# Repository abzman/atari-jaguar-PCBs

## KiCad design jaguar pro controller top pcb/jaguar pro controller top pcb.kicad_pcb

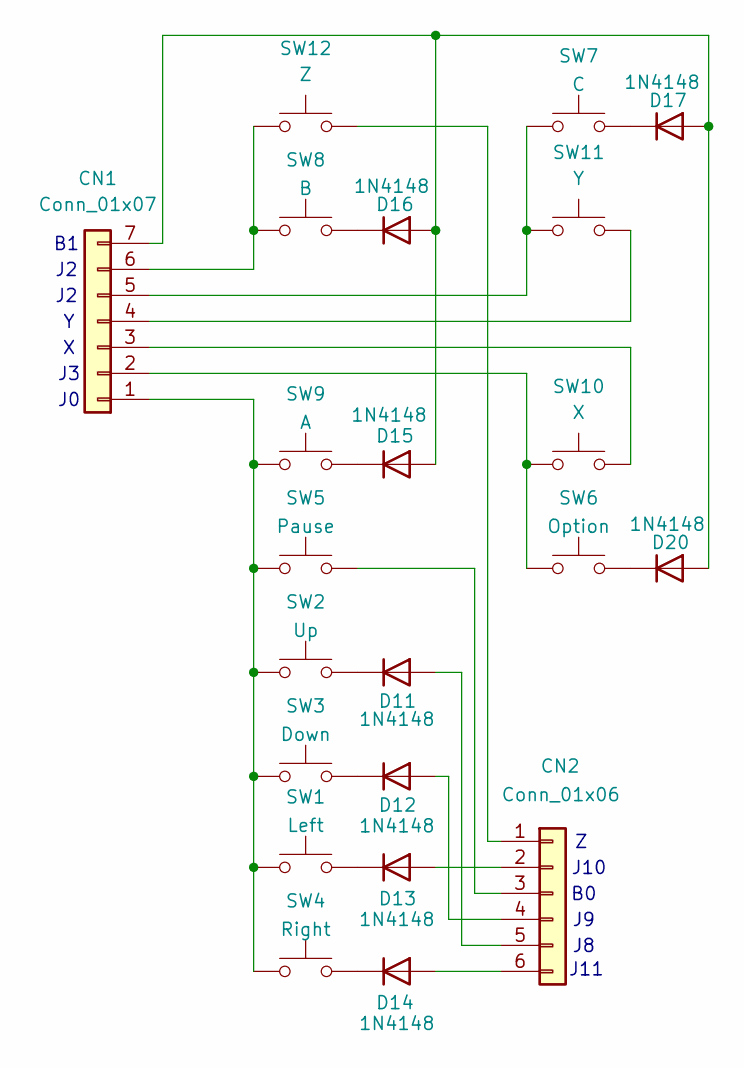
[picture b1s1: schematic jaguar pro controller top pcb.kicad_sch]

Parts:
CN1: Conn_01x07; PinHeader_1x07_P2.00mm_Vertical
CN2: Conn_01x06; PinHeader_1x06_P2.00mm_Vertical
D11, D12, D13, D14, D16, D17, D20: 1N4148; D_DO-35_SOD27_P5.62mm_Horizontal
D15: 1N4148; D_DO-35_SOD27_P9.50mm_Horizontal
SW1: Left; jaguar pro dpad
SW2: Up; jaguar pro dpad
SW3: Down; jaguar pro dpad
SW4: Right; jaguar pro dpad
SW5: Pause; jaguar pro keypad
SW6: Option; jaguar pro keypad
SW7: C; Jaguar pro ABC button
SW8: B; Jaguar pro ABC button
SW9: A; Jaguar pro ABC button
SW10: X; Jaguar pro ABC button
SW11: Y; Jaguar pro ABC button
SW12: Z; Jaguar pro ABC button

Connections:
unnamed: CN2.5, D11.2 (A)
unnamed: D11.1 (K), SW2.2
unnamed: CN2.4, D12.2 (A)
unnamed: D12.1 (K), SW3.2
unnamed: CN2.2, D13.2 (A)
unnamed: D13.1 (K), SW1.2
unnamed: CN2.6, D14.2 (A)
unnamed: D14.1 (K), SW4.2
unnamed: CN1.7, D15.2 (A), D16.2 (A), D17.2 (A), D20.2 (A)
unnamed: D15.1 (K), SW9.2
unnamed: D16.1 (K), SW8.2
unnamed: D17.1 (K), SW7.2
unnamed: D20.1 (K), SW6.1
unnamed: CN1.1, SW1.1, SW2.1, SW3.1, SW4.1, SW5.2, SW9.1
unnamed: CN1.2, SW6.2, SW10.1
unnamed: CN1.3, SW10.2
unnamed: CN1.4, SW11.2
unnamed: CN1.5, SW7.1, SW11.1
unnamed: CN1.6, SW8.1, SW12.1
unnamed: CN2.1, SW12.2
unnamed: CN2.3, SW5.1

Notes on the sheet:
J10
J11

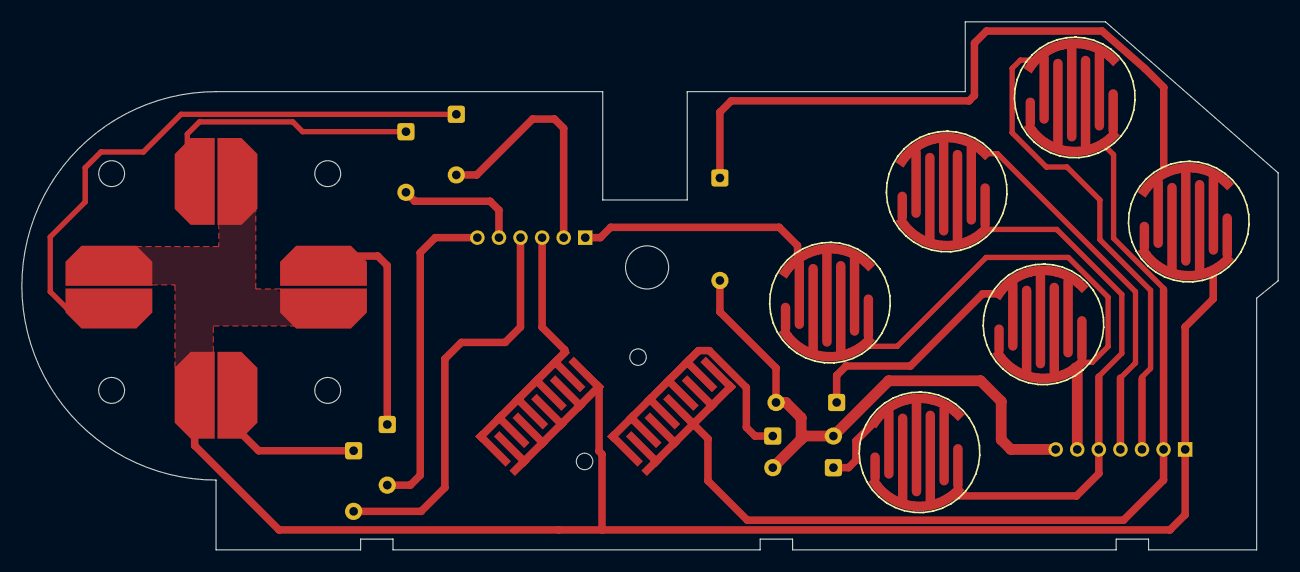
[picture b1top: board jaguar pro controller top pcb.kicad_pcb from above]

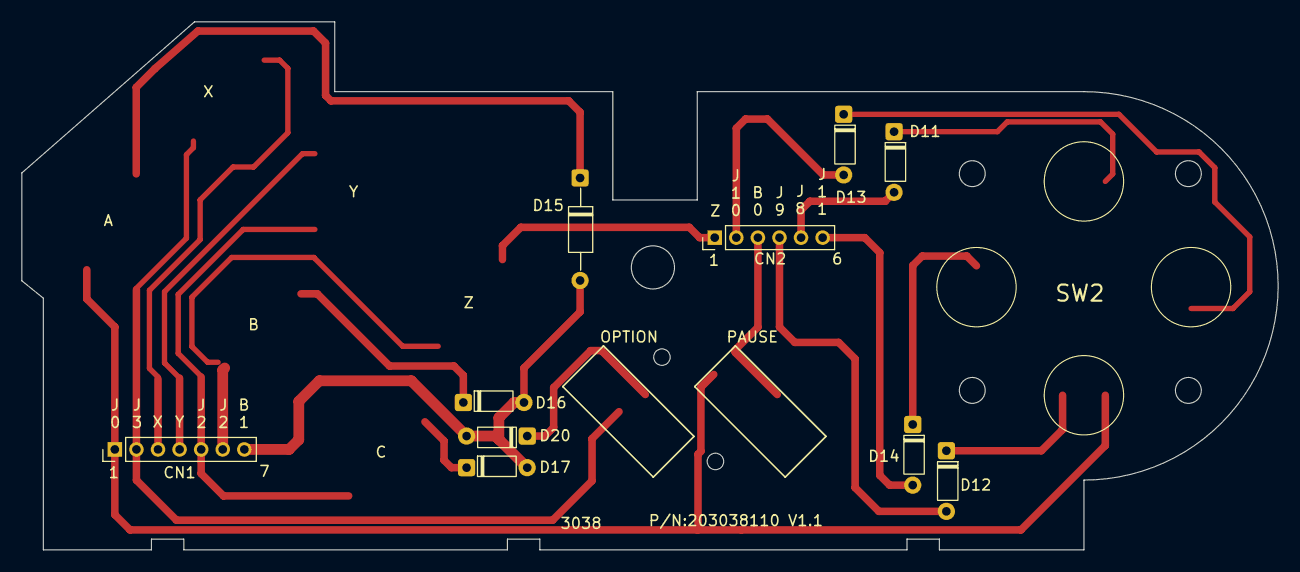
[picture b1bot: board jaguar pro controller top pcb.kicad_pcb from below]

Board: 2 copper layers, 116.4 x 48.9 mm, 22 parts (10 on the bottom side), 21 nets.

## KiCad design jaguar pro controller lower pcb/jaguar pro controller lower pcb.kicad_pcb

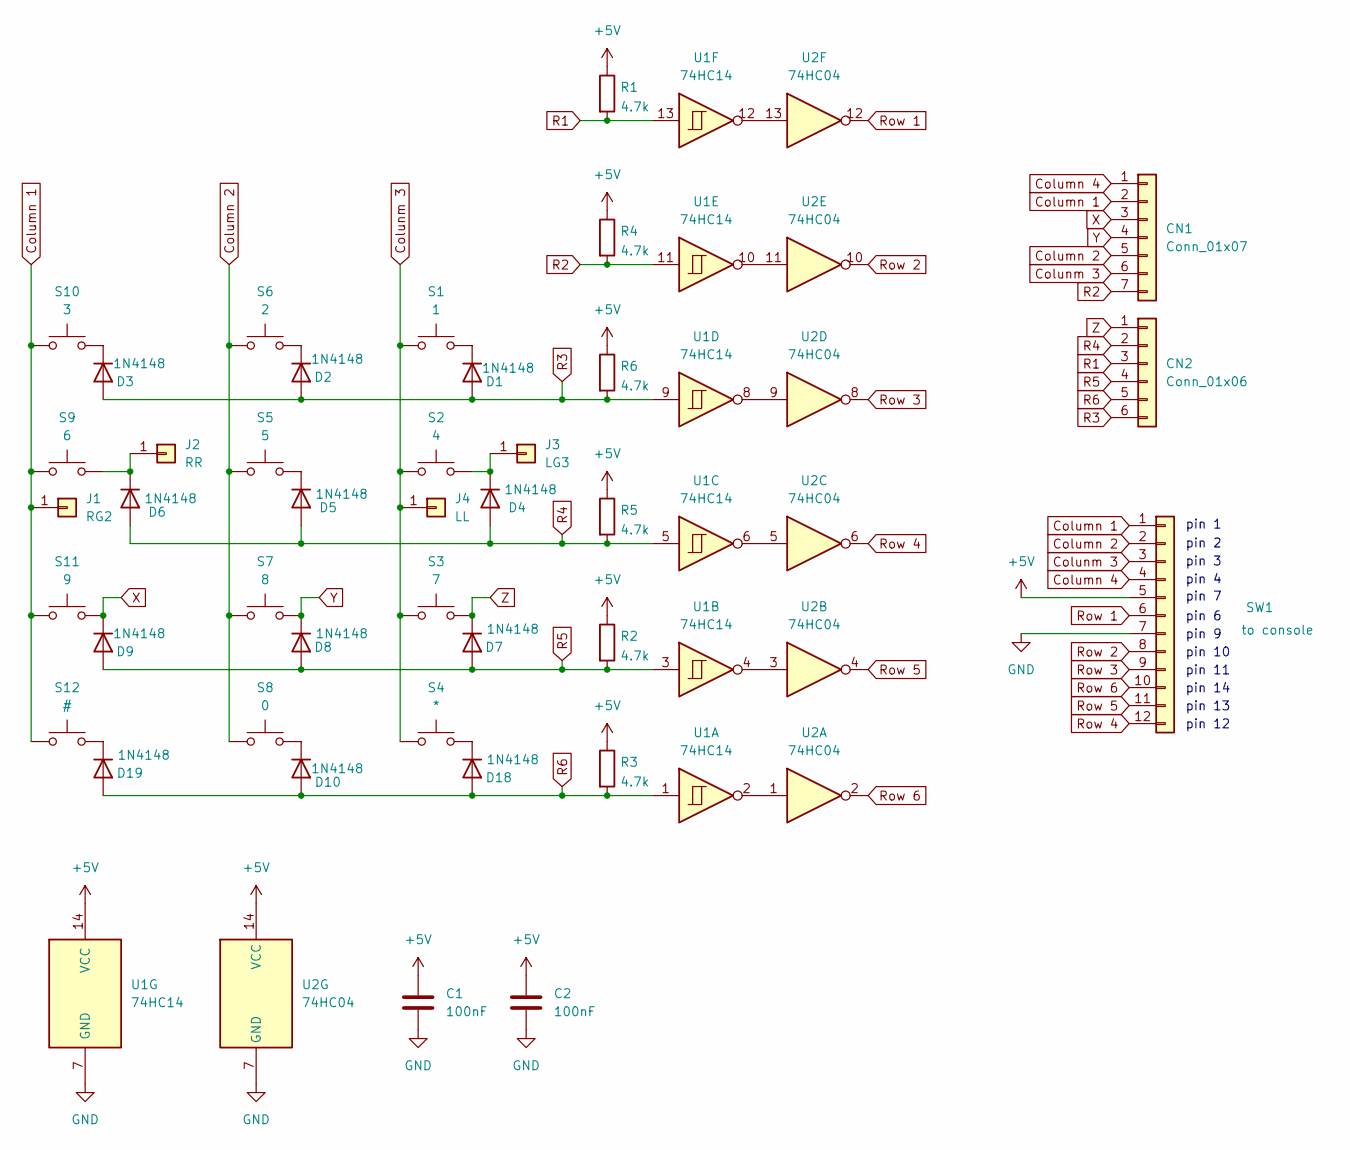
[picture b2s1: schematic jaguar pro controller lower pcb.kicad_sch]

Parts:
C1, C2: 100nF; C_Disc_D4.3mm_W1.9mm_P5.00mm
CN1: Conn_01x07; PinHeader_1x07_P2.00mm_Vertical
CN2: Conn_01x06; PinHeader_1x06_P2.00mm_Vertical
D1, D2, D3, D4, D5, D6, D7, D8, D9, D10, D18, D19: 1N4148; D_DO-35_SOD27_P9.50mm_Horizontal
J1: RG2; PinSocket_1x01_P2.00mm_Vertical
J2: RR; PinSocket_1x01_P2.00mm_Vertical
J3: LG3; PinSocket_1x01_P2.00mm_Vertical
J4: LL; PinSocket_1x01_P2.00mm_Vertical
R1, R2, R3: 4.7k; R_Axial_DIN0207_L6.3mm_D2.5mm_P2.54mm_Vertical
R4, R5, R6: 4.7k; R_Axial_DIN0204_L3.6mm_D1.6mm_P12.89mm_Horizontal
S1: 1; jaguar pro keypad
S2: 4; jaguar pro keypad
S3: 7; jaguar pro keypad
S4: *; jaguar pro keypad
S5: 5; jaguar pro keypad
S6: 2; jaguar pro keypad
S7: 8; jaguar pro keypad
S8: 0; jaguar pro keypad
S9: 6; jaguar pro keypad
S10: 3; jaguar pro keypad
S11: 9; jaguar pro keypad
S12: #; jaguar pro keypad
SW1: to console; PinHeader_1x12_P2.54mm_Vertical
U1: 74HC14; DIP-14_W7.62mm
U2: 74HC04; DIP-14_W7.62mm

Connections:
+5V: C1.1, C2.1, R1.1, R2.1, R3.1, R4.1, R5.1, R6.1, SW1.5, U1.14 (VCC), U2.14 (VCC)
Column 1: CN1.2, J1.1, S9.2, S10.1, S11.1, S12.1, SW1.1
Column 2: CN1.5, S5.2, S6.2, S7.1, S8.1, SW1.2
Column 4: CN1.1, SW1.4
Colunm 3: CN1.6, J4.1, S1.1, S2.2, S3.1, S4.1, SW1.3
GND: C1.2, C2.2, SW1.7, U1.7 (GND), U2.7 (GND)
unnamed: D1.1 (K), S1.2
unnamed: D2.1 (K), S6.1
unnamed: D3.1 (K), S10.2
unnamed: D4.1 (K), J3.1, S2.1
unnamed: D5.1 (K), S5.1
unnamed: D6.1 (K), J2.1, S9.1
unnamed: D10.1 (K), S8.2
unnamed: D18.1 (K), S4.2
unnamed: D19.1 (K), S12.2
unnamed: U1.2, U2.1
unnamed: U1.4, U2.3
unnamed: U1.6, U2.5
unnamed: U1.8, U2.9
unnamed: U1.10, U2.11
unnamed: U1.12, U2.13
R1: CN2.3, R1.2, U1.13
R2: CN1.7, R4.2, U1.11
R3: CN2.6, D1.2 (A), D2.2 (A), D3.2 (A), R6.2, U1.9
R4: CN2.2, D4.2 (A), D5.2 (A), D6.2 (A), R5.2, U1.5
R5: CN2.4, D7.2 (A), D8.2 (A), D9.2 (A), R2.2, U1.3
R6: CN2.5, D10.2 (A), D18.2 (A), D19.2 (A), R3.2, U1.1
Row 1: SW1.6, U2.12
Row 2: SW1.8, U2.10
Row 3: SW1.9, U2.8
Row 4: SW1.12, U2.6
Row 5: SW1.11, U2.4
Row 6: SW1.10, U2.2
X: CN1.3, D9.1 (K), S11.2
Y: CN1.4, D8.1 (K), S7.2
Z: CN2.1, D7.1 (K), S3.2

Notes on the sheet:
pin 3
pin 11
pin 14
pin 1
pin 12
pin 7
pin 13
pin 6
pin 9
pin 4
pin 10
pin 2

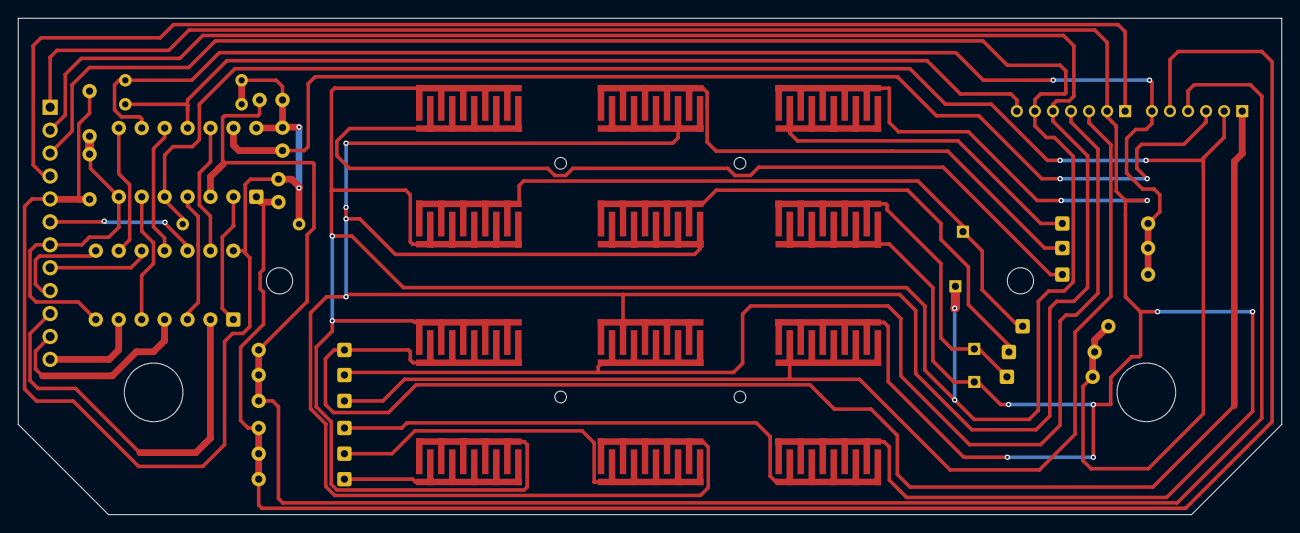
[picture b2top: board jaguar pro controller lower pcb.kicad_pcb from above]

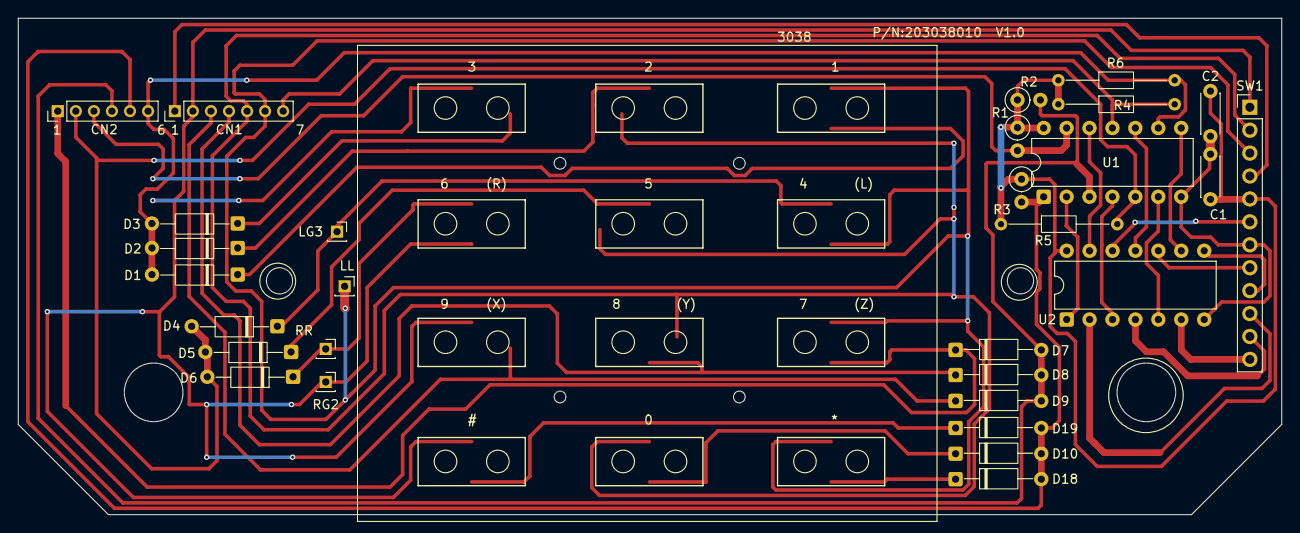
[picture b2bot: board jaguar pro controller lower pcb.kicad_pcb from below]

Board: 2 copper layers, 140.0 x 55.0 mm, 41 parts (29 on the bottom side), 36 nets.

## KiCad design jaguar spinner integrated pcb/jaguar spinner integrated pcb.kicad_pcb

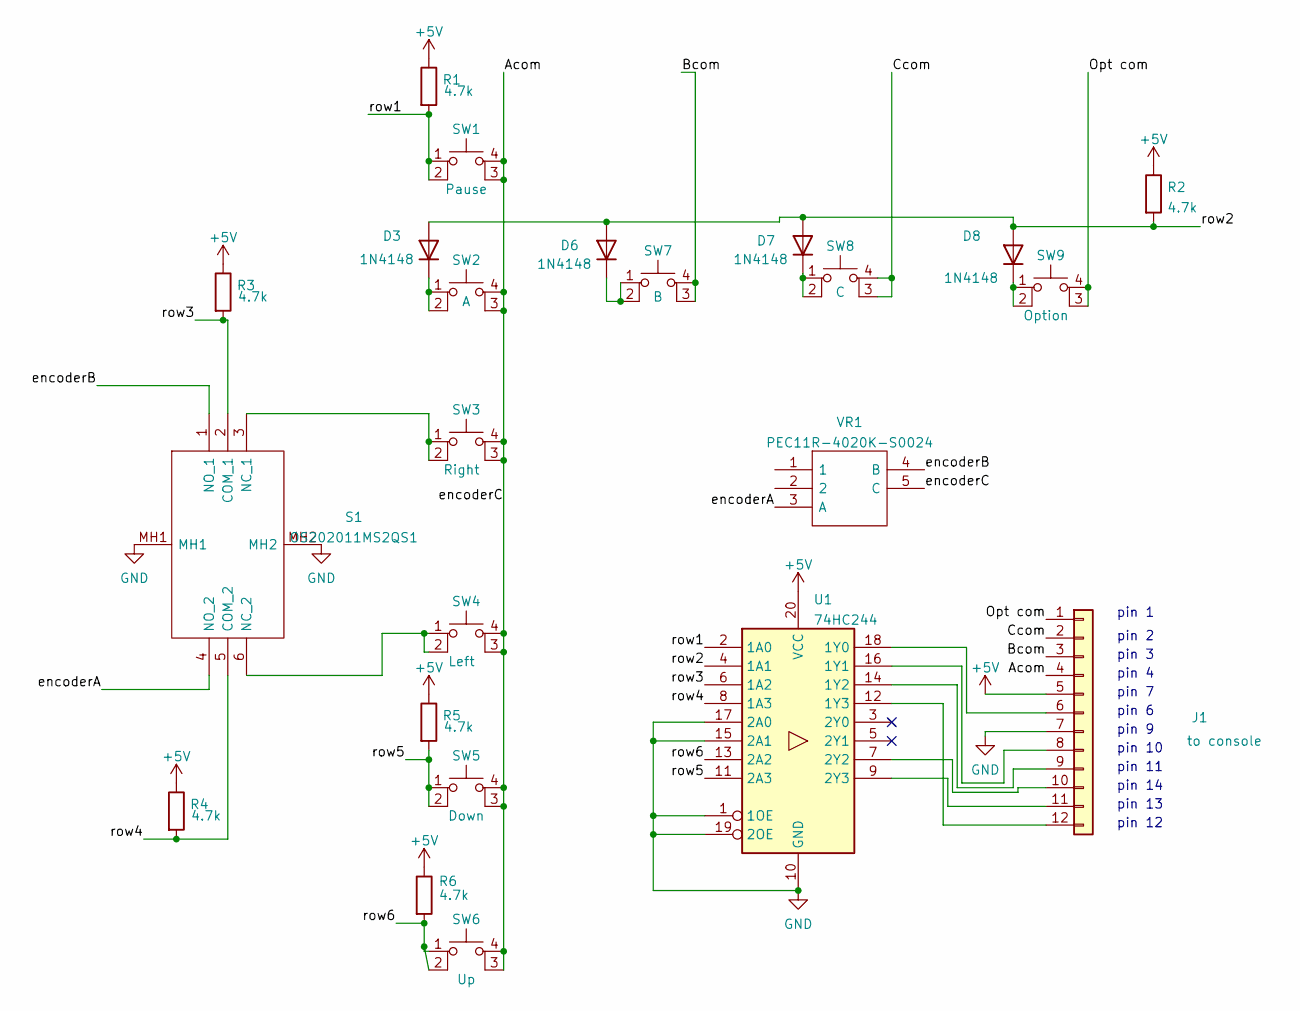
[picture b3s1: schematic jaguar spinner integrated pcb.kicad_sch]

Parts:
D3, D6, D7, D8: 1N4148; D_DO-35_SOD27_P7.62mm_Horizontal
J1: to console; PinHeader_1x12_P2.54mm_Vertical
R1, R2, R3, R4, R5, R6: 4.7k; R_0603_1608Metric
S1: OS202011MS2QS1; Mouser Part Number 611-OS202011MS2QS1
SW1: Pause; SW_TH_Tactile_Omron_B3F-10xx
SW2: A; SW_TH_Tactile_Omron_B3F-10xx
SW3: Right; SW_TH_Tactile_Omron_B3F-10xx
SW4: Left; SW_TH_Tactile_Omron_B3F-10xx
SW5: Down; SW_TH_Tactile_Omron_B3F-10xx
SW6: Up; SW_TH_Tactile_Omron_B3F-10xx
SW7: B; SW_TH_Tactile_Omron_B3F-10xx
SW8: C; SW_TH_Tactile_Omron_B3F-10xx
SW9: Option; SW_TH_Tactile_Omron_B3F-10xx
U1: 74HC244; DIP-20_W7.62mm
VR1: PEC11R-4020K-S0024; PEC11R-4XXXK-SXXXX; Mouser Part Number 652-PEC11R-4020K-S24

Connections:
+5V: J1.5, R1.1, R2.1, R3.1, R4.1, R5.1, R6.1, U1.20 (VCC)
/Acom: J1.4, SW1.3 (K), SW1.4 (A), SW2.3 (K), SW2.4 (A), SW3.3 (K), SW3.4 (A), SW4.3 (K), SW4.4 (A), SW5.3 (K), SW5.4 (A), SW6.3 (K), SW6.4 (A), VR1.5 (C)
/Bcom: J1.3, SW7.3 (K), SW7.4 (A)
/Ccom: J1.2, SW8.3 (K), SW8.4 (A)
/Opt com: J1.1, SW9.3 (K), SW9.4 (A)
/encoderA: S1.4 (NO_2), VR1.3 (A)
/encoderB: S1.1 (NO_1), VR1.4 (B)
/row1: R1.2, SW1.1, SW1.2, U1.2 (1A0)
/row2: D3.2 (A), D6.2 (A), D7.2 (A), D8.2 (A), R2.2, U1.4 (1A1)
/row3: R3.2, S1.2 (COM_1), U1.6 (1A2)
/row4: R4.2, S1.5 (COM_2), U1.8 (1A3)
/row5: R5.2, SW5.1, SW5.2, U1.11 (2A3)
/row6: R6.2, SW6.1, SW6.2, U1.13 (2A2)
GND: J1.7, S1.MH1, S1.MH2, U1.1 (1OE), U1.10 (GND), U1.15 (2A1), U1.17 (2A0), U1.19 (2OE), VR1.6, VR1.7
unnamed: D3.1 (K), SW2.1, SW2.2
unnamed: D7.1 (K), SW8.1, SW8.2
unnamed: D8.1 (K), SW9.1, SW9.2
unnamed: J1.6, U1.18 (1Y0)
unnamed: J1.8, U1.16 (1Y1)
unnamed: J1.9, U1.14 (1Y2)
unnamed: J1.10, U1.7 (2Y2)
unnamed: J1.11, U1.9 (2Y3)
unnamed: J1.12, U1.12 (1Y3)
unnamed: S1.3 (NC_1), SW3.1, SW3.2
unnamed: S1.6 (NC_2), SW4.1, SW4.2
unnamed: D6.1 (K), SW7.1, SW7.2

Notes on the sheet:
pin 11
pin 3
pin 7
pin 10
pin 2
pin 9
pin 13
pin 6
pin 12
pin 4
pin 14
pin 1

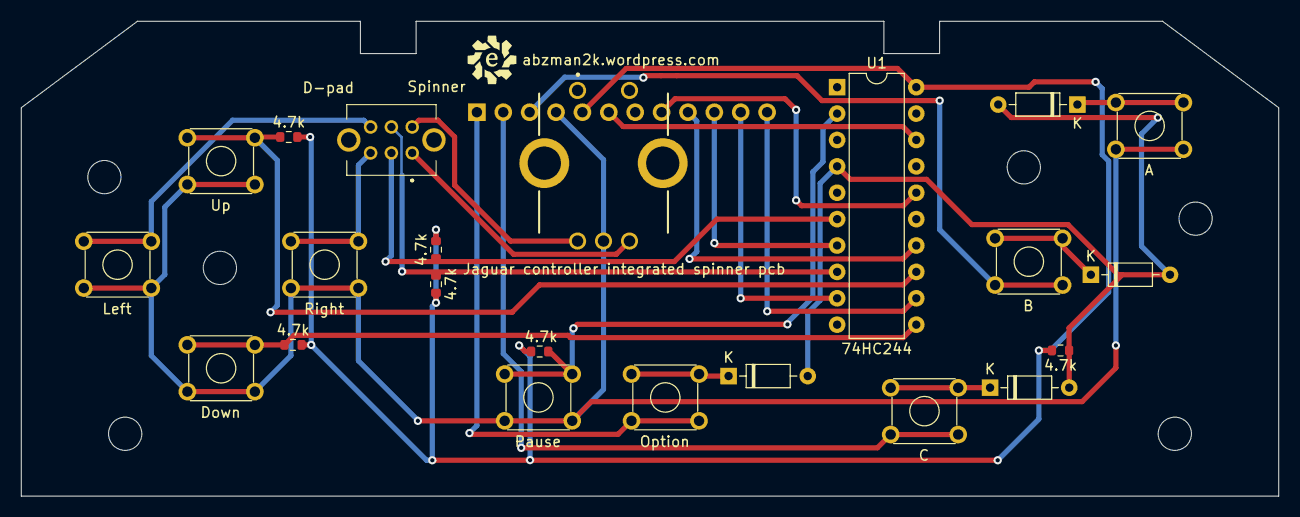
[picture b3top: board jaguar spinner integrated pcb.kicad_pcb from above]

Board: 2 copper layers, 121.1 x 45.7 mm, 23 parts (1 on the bottom side), 26 nets.

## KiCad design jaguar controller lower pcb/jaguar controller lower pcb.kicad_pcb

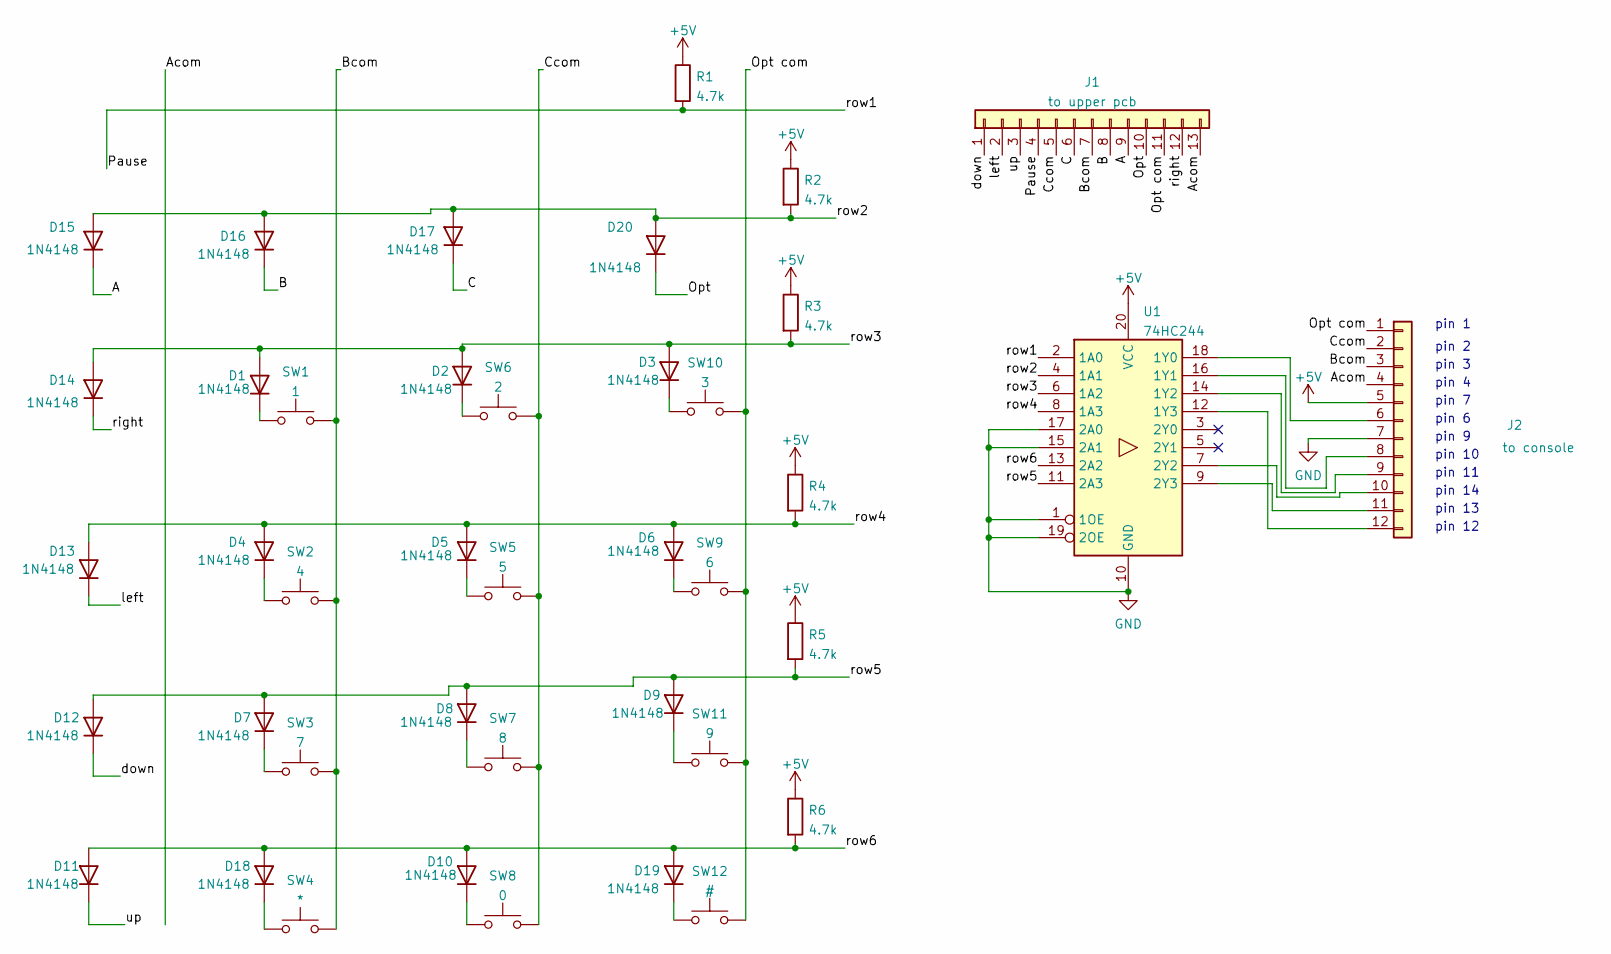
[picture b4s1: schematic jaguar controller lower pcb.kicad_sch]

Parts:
D1, D2, D3, D4, D5, D6, D7, D8, D9, D10, D11, D12, D13, D14, D15, D16, D17, D18, D19, D20: 1N4148; D_DO-35_SOD27_P7.62mm_Horizontal
J1: to upper pcb; PinHeader_1x13_P2.00mm_Vertical
J2: to console; PinHeader_1x12_P2.54mm_Vertical
R1, R2, R3, R4, R5, R6: 4.7k; R_Axial_DIN0207_L6.3mm_D2.5mm_P10.16mm_Horizontal
SW1: 1; jaguar keypad button
SW2: 4; jaguar keypad button
SW3: 7; jaguar keypad button
SW4: *; jaguar keypad button
SW5: 5; jaguar keypad button
SW6: 2; jaguar keypad button
SW7: 8; jaguar keypad button
SW8: 0; jaguar keypad button
SW9: 6; jaguar keypad button
SW10: 3; jaguar keypad button
SW11: 9; jaguar keypad button
SW12: #; jaguar keypad button
U1: 74HC244; DIP-20_W7.62mm

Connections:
+5V: J2.5, R1.1, R2.1, R3.1, R4.1, R5.1, R6.1, U1.20 (VCC)
/A: D15.1 (K), J1.9
/Acom: J1.13, J2.4
/B: D16.1 (K), J1.8
/Bcom: J1.7, J2.3, SW1.2, SW2.2, SW3.2, SW4.2
/C: D17.1 (K), J1.6
/Ccom: J1.5, J2.2, SW5.2, SW6.2, SW7.2, SW8.2
/Opt: D20.1 (K), J1.10
/Opt com: J1.11, J2.1, SW9.2, SW10.2, SW11.2, SW12.2
/Pause: J1.4, R1.2, U1.2 (1A0)
/down: D12.1 (K), J1.1
/left: D13.1 (K), J1.2
/right: D14.1 (K), J1.12
/row2: D15.2 (A), D16.2 (A), D17.2 (A), D20.2 (A), R2.2, U1.4 (1A1)
/row3: D1.2 (A), D2.2 (A), D3.2 (A), D14.2 (A), R3.2, U1.6 (1A2)
/row4: D4.2 (A), D5.2 (A), D6.2 (A), D13.2 (A), R4.2, U1.8 (1A3)
/row5: D7.2 (A), D8.2 (A), D9.2 (A), D12.2 (A), R5.2, U1.11 (2A3)
/row6: D10.2 (A), D11.2 (A), D18.2 (A), D19.2 (A), R6.2, U1.13 (2A2)
/up: D11.1 (K), J1.3
GND: J2.7, U1.1 (1OE), U1.10 (GND), U1.15 (2A1), U1.17 (2A0), U1.19 (2OE)
unnamed: D1.1 (K), SW1.1
unnamed: D2.1 (K), SW6.1
unnamed: D3.1 (K), SW10.1
unnamed: D4.1 (K), SW2.1
unnamed: D5.1 (K), SW5.1
unnamed: D6.1 (K), SW9.1
unnamed: D7.1 (K), SW3.1
unnamed: D8.1 (K), SW7.1
unnamed: D9.1 (K), SW11.1
unnamed: D10.1 (K), SW8.1
unnamed: D18.1 (K), SW4.1
unnamed: D19.1 (K), SW12.1
unnamed: J2.6, U1.18 (1Y0)
unnamed: J2.8, U1.16 (1Y1)
unnamed: J2.9, U1.14 (1Y2)
unnamed: J2.10, U1.7 (2Y2)
unnamed: J2.11, U1.9 (2Y3)
unnamed: J2.12, U1.12 (1Y3)

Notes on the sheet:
pin 6
pin 13
pin 1
pin 9
pin 14
pin 10
pin 2
pin 11
pin 3
pin 4
pin 12
pin 7

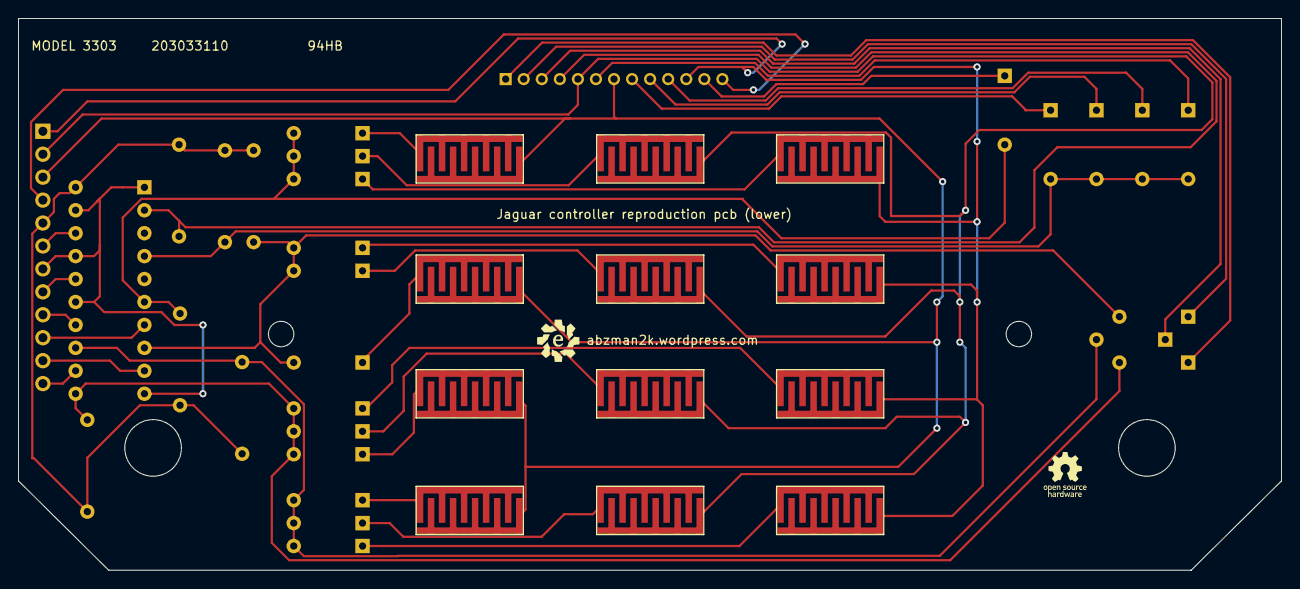
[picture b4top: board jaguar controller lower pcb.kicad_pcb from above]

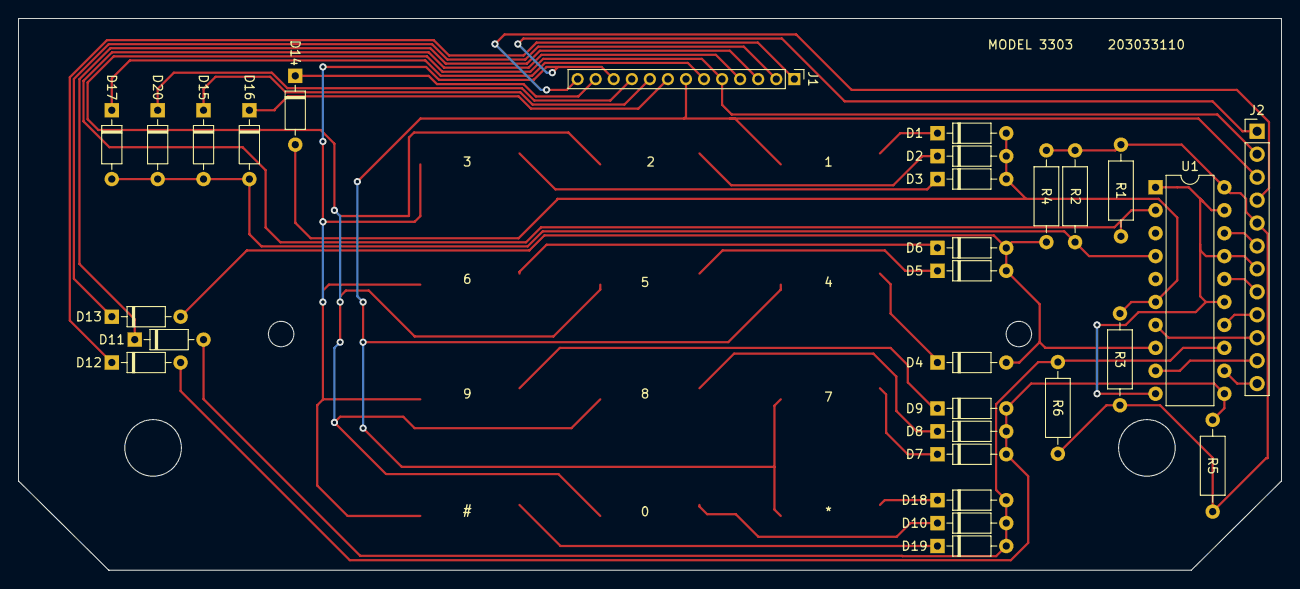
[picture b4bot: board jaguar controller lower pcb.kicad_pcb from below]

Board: 2 copper layers, 139.9 x 61.1 mm, 41 parts (29 on the bottom side), 38 nets.

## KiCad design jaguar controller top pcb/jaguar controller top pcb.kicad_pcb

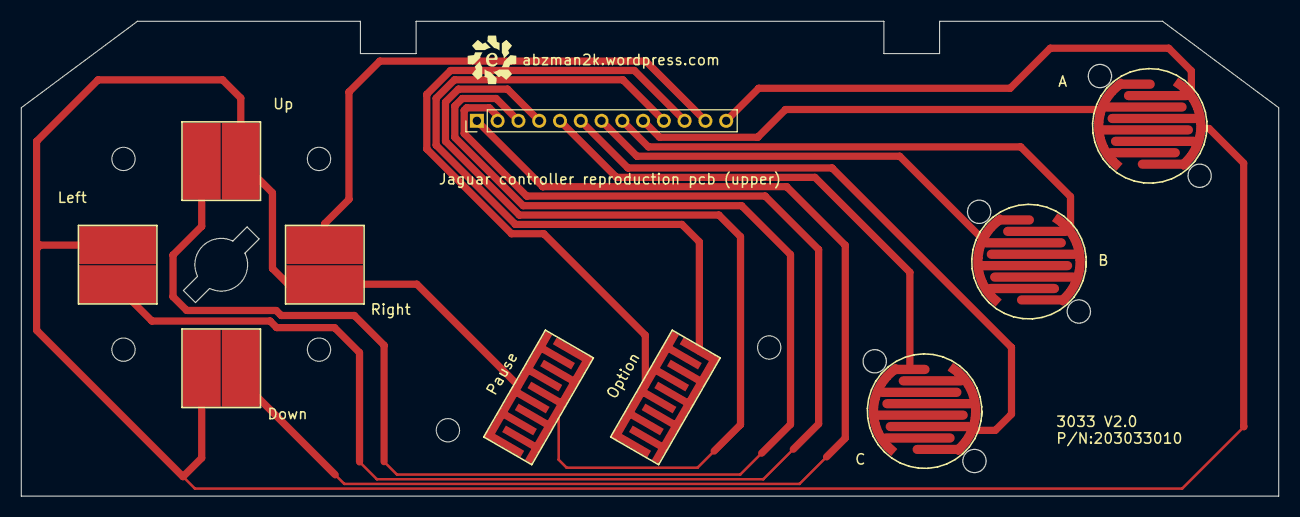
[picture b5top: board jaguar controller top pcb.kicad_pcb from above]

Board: 2 copper layers, 121.0 x 45.7 mm, 10 parts (0 on the bottom side), 13 nets.

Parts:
J1: Conn_01x13; PinHeader_1x13_P2.00mm_Vertical
SW1: Left; jaguar dpad
SW2: Up; jaguar dpad
SW3: Down; jaguar dpad
SW4: Right; jaguar dpad
SW5: Pause; jaguar keypad button
SW6: Option; jaguar keypad button
SW7: C; jaguar abc
SW8: B; jaguar abc
SW9: A; jaguar abc

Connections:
unnamed: J1.1, SW3.2
unnamed: J1.2, SW1.2
unnamed: J1.3, SW2.1
unnamed: J1.4, SW5.2
unnamed: J1.5, SW7.1
unnamed: J1.6, SW7.2
unnamed: J1.7, SW8.1
unnamed: J1.8, SW8.2
unnamed: J1.9, SW9.1
unnamed: J1.10, SW6.2
unnamed: J1.11, SW6.1
unnamed: J1.12, SW4.2
unnamed: J1.13, SW1.1, SW2.2, SW3.1, SW4.1, SW5.1, SW9.2

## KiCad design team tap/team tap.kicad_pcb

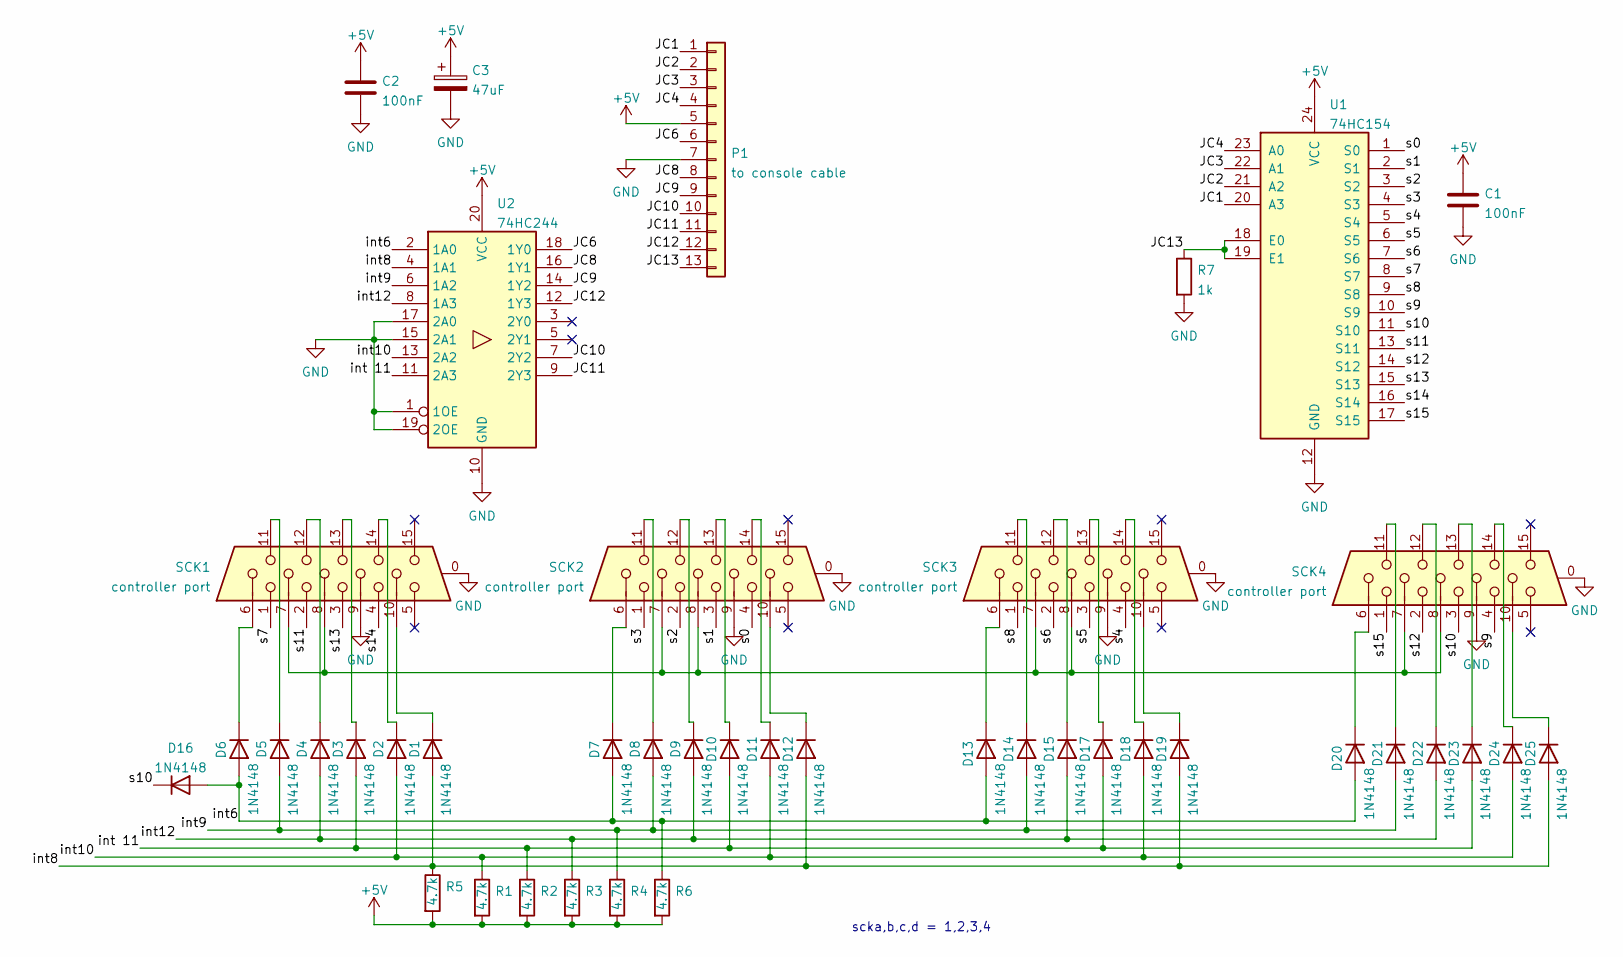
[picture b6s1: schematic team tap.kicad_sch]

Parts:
C1, C2: 100nF; C_Disc_D4.3mm_W1.9mm_P5.00mm
C3: 47uF; CP_Radial_D5.0mm_P2.50mm
D1, D2, D3, D4, D5, D6, D7, D8, D9, D10, D11, D12, D13, D14, D15, D16, D17, D18, D19, D20, D21, D22, D23, D24, D25: 1N4148; D_DO-35_SOD27_P7.62mm_Horizontal
P1: to console cable; PinHeader_1x13_P2.54mm_Vertical
R1, R2, R3, R4, R5, R6: 4.7k; R_Axial_DIN0204_L3.6mm_D1.6mm_P2.54mm_Vertical
R7: 1k; R_Axial_DIN0204_L3.6mm_D1.6mm_P2.54mm_Vertical
SCK1, SCK2, SCK3, SCK4: controller port; DSUB-15-HD_Female_Horizontal_P2.29x1.98mm_EdgePinOffset8.35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
U1: 74HC154; DIP-24_W15.24mm
U2: 74HC244; DIP-20_W7.62mm

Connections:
+5V: C1.1, C2.1, C3.1, P1.5, R1.2, R2.2, R3.2, R4.2, R5.2, R6.2, U1.24 (VCC), U2.20 (VCC)
/JC1: P1.1, U1.20 (A3)
/JC2: P1.2, U1.21 (A2)
/JC3: P1.3, U1.22 (A1)
/JC4: P1.4, U1.23 (A0)
/JC6: P1.6, U2.18 (1Y0)
/JC8: P1.8, U2.16 (1Y1)
/JC9: P1.9, U2.14 (1Y2)
/JC10: P1.10, U2.7 (2Y2)
/JC11: P1.11, U2.9 (2Y3)
/JC12: P1.12, U2.12 (1Y3)
/JC13: P1.13, R7.1, U1.18 (E0), U1.19 (E1)
/int6: D6.2 (A), D7.2 (A), D13.2 (A), D16.2 (A), D20.2 (A), R6.1, U2.2 (1A0)
/int8: D1.2 (A), D12.2 (A), D19.2 (A), D25.2 (A), R5.1, U2.4 (1A1)
/int9: D5.2 (A), D8.2 (A), D14.2 (A), D21.2 (A), R4.1, U2.6 (1A2)
/int10: D2.2 (A), D11.2 (A), D18.2 (A), D24.2 (A), R1.1, U2.13 (2A2)
/int12: D4.2 (A), D9.2 (A), D15.2 (A), D22.2 (A), R3.1, U2.8 (1A3)
/int 11: D3.2 (A), D10.2 (A), D17.2 (A), D23.2 (A), R2.1, U2.11 (2A3)
/s0: SCK2.4, U1.1 (S0)
/s1: SCK2.3, U1.2 (S1)
/s2: SCK2.2, U1.3 (S2)
/s3: SCK2.1, U1.4 (S3)
/s4: SCK3.4, U1.5 (S4)
/s5: SCK3.3, U1.6 (S5)
/s6: SCK3.2, U1.7 (S6)
/s7: SCK1.1, U1.8 (S7)
/s8: SCK3.1, U1.9 (S8)
/s9: SCK4.4, U1.10 (S9)
/s10: D16.1 (K), SCK4.3, U1.11 (S10)
/s11: SCK1.2, U1.13 (S11)
/s12: SCK4.2, U1.14 (S12)
/s13: SCK1.3, U1.15 (S13)
/s14: SCK1.4, U1.16 (S14)
/s15: SCK4.1, U1.17 (S15)
GND: C1.2, C2.2, C3.2, P1.7, R7.2, SCK1.0, SCK1.9, SCK2.0, SCK2.9, SCK3.0, SCK3.9, SCK4.0, SCK4.9, U1.12 (GND), U2.1 (1OE), U2.10 (GND), U2.15 (2A1), U2.17 (2A0), U2.19 (2OE)
unnamed: D1.1 (K), SCK1.10
unnamed: D2.1 (K), SCK1.14
unnamed: D3.1 (K), SCK1.13
unnamed: D4.1 (K), SCK1.12
unnamed: D5.1 (K), SCK1.11
unnamed: D6.1 (K), SCK1.6
unnamed: D8.1 (K), SCK2.11
unnamed: D9.1 (K), SCK2.12
unnamed: D10.1 (K), SCK2.13
unnamed: D11.1 (K), SCK2.14
unnamed: D12.1 (K), SCK2.10
unnamed: D21.1 (K), SCK4.11
unnamed: D22.1 (K), SCK4.12
unnamed: D23.1 (K), SCK4.13
unnamed: D24.1 (K), SCK4.14
unnamed: D7.1 (K), SCK2.6
unnamed: D13.1 (K), SCK3.6
unnamed: D19.1 (K), SCK3.10
unnamed: D14.1 (K), SCK3.11
unnamed: D15.1 (K), SCK3.12
unnamed: D17.1 (K), SCK3.13
unnamed: D18.1 (K), SCK3.14
unnamed: D20.1 (K), SCK4.6
unnamed: SCK1.7, SCK1.8, SCK2.7, SCK2.8, SCK3.7, SCK3.8, SCK4.7, SCK4.8
unnamed: D25.1 (K), SCK4.10

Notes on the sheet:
scka,b,c,d = 1,2,3,4

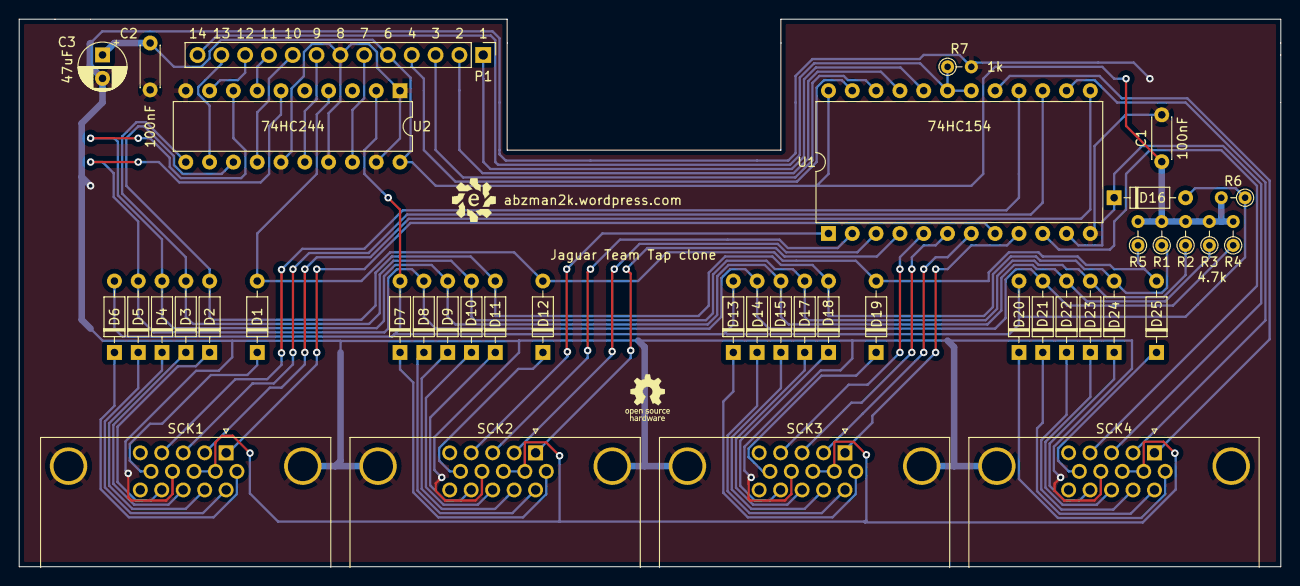
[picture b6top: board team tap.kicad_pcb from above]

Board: 2 copper layers, 134.6 x 58.4 mm, 42 parts (0 on the bottom side), 60 nets.

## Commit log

2022-02-28 multitap schematic done
2022-03-01 fixed layout and added pcb
2022-03-01 jaguar controller PCB start
2022-03-13 finished all PCBs for this round
2022-03-13 generated gerbers
2022-03-14 gerber zips
2022-11-25 added gitignore for kicad
2024-07-28 updated to later kicad
2026-02-08 added jaguar pro controller boards
